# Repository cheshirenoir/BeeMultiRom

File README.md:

# BeeMultiRom
27c128 to 27c2001 adapter with selector for choosing between 16 different ROM images.
CC BY SA created in KiCAD
TESTED OK! If you use it in the IC22 socket of a PC85b, you can use double sized ROMs. If you use single sized ROMs, you can then access the lower ROM with PAK4 and the upper ROM with PAK12
This new version uses turned pins (from turned pin sockets. Just cut them mout with side cutters) and will just fit inside the case of a Microbee. 

Assembly instructions here: https://ilike8bits.com/assembling-the-microbee-multirom/

CC BY SA

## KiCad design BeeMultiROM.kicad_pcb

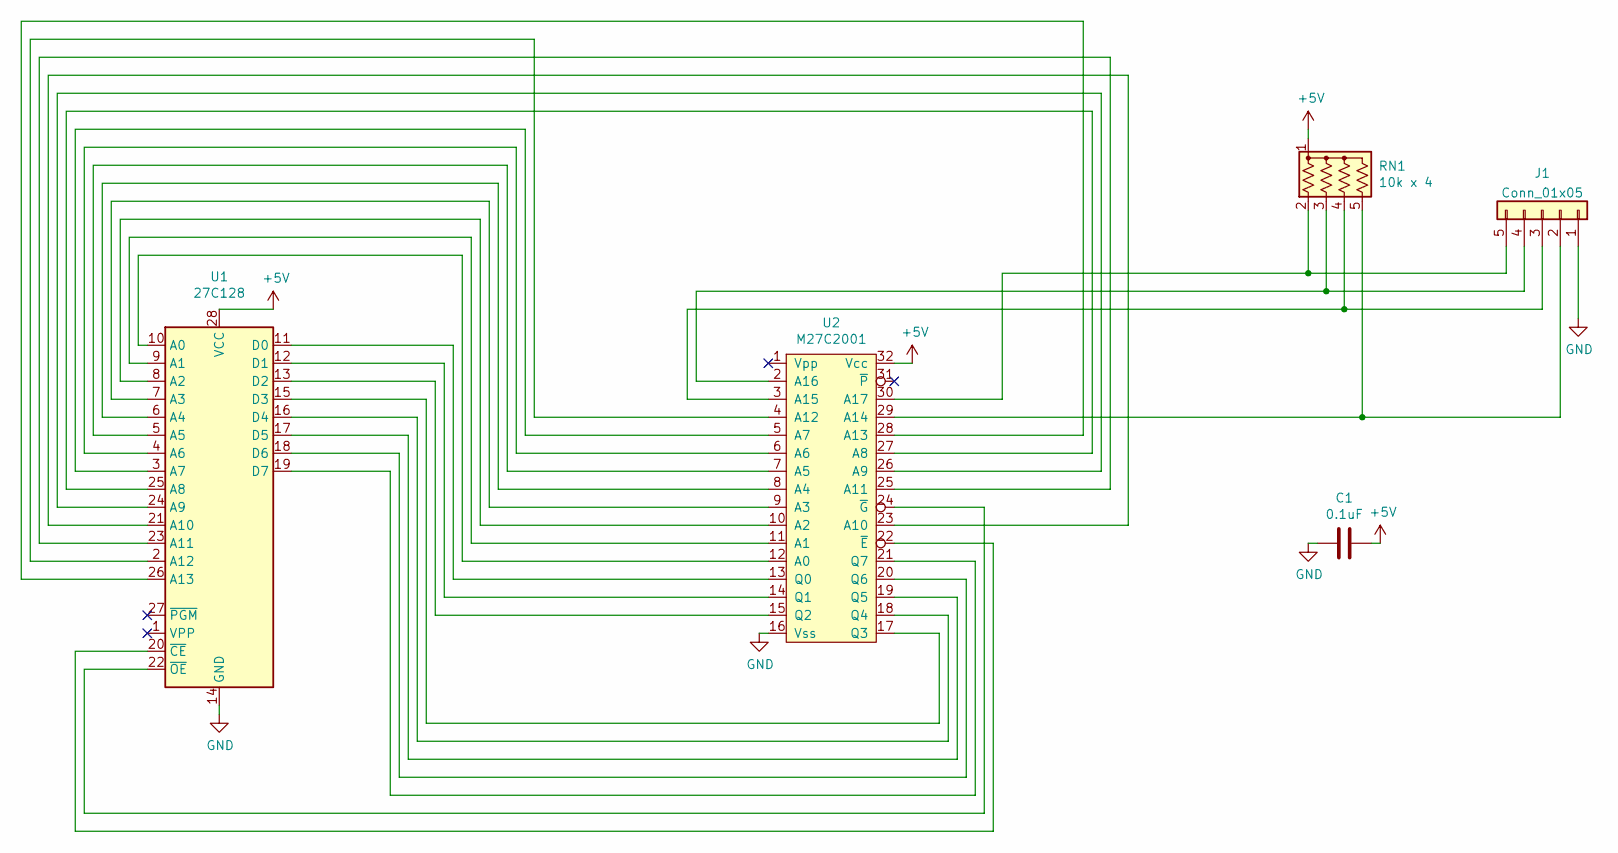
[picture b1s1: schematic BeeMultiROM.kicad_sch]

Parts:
C1: 0.1uF; C_Disc_D8.0mm_W2.5mm_P5.00mm
J1: Conn_01x05; PinHeader_1x05_P2.54mm_Vertical
RN1: 10k x 4; R_Array_SIP5
U1: 27C128; DIP-28_W15.24mm
U2: M27C2001; DIP-32_LP_FATBOY

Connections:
+5V: C1.1, RN1.1 (common), U1.28 (VCC), U2.32 (Vcc)
GND: C1.2, J1.1, U1.14 (GND), U2.16 (Vss)
unnamed: J1.2, RN1.5 (R4), U2.29 (A14)
unnamed: J1.3, RN1.4 (R3), U2.3 (A15)
unnamed: J1.4, RN1.3 (R2), U2.2 (A16)
unnamed: J1.5, RN1.2 (R1), U2.30 (A17)
unnamed: U1.2 (A12), U2.4 (A12)
unnamed: U1.3 (A7), U2.5 (A7)
unnamed: U1.4 (A6), U2.6 (A6)
unnamed: U1.5 (A5), U2.7 (A5)
unnamed: U1.6 (A4), U2.8 (A4)
unnamed: U1.7 (A3), U2.9 (A3)
unnamed: U1.8 (A2), U2.10 (A2)
unnamed: U1.9 (A1), U2.11 (A1)
unnamed: U1.10 (A0), U2.12 (A0)
unnamed: U1.11 (D0), U2.13 (Q0)
unnamed: U1.12 (D1), U2.14 (Q1)
unnamed: U1.13 (D2), U2.15 (Q2)
unnamed: U1.15 (D3), U2.17 (Q3)
unnamed: U1.16 (D4), U2.18 (Q4)
unnamed: U1.17 (D5), U2.19 (Q5)
unnamed: U1.18 (D6), U2.20 (Q6)
unnamed: U1.19 (D7), U2.21 (Q7)
unnamed: U1.20 (~CE), U2.22 (~E)
unnamed: U1.21 (A10), U2.23 (A10)
unnamed: U1.22 (~OE), U2.24 (~G)
unnamed: U1.23 (A11), U2.25 (A11)
unnamed: U1.24 (A9), U2.26 (A9)
unnamed: U1.25 (A8), U2.27 (A8)
unnamed: U1.26 (A13), U2.28 (A13)

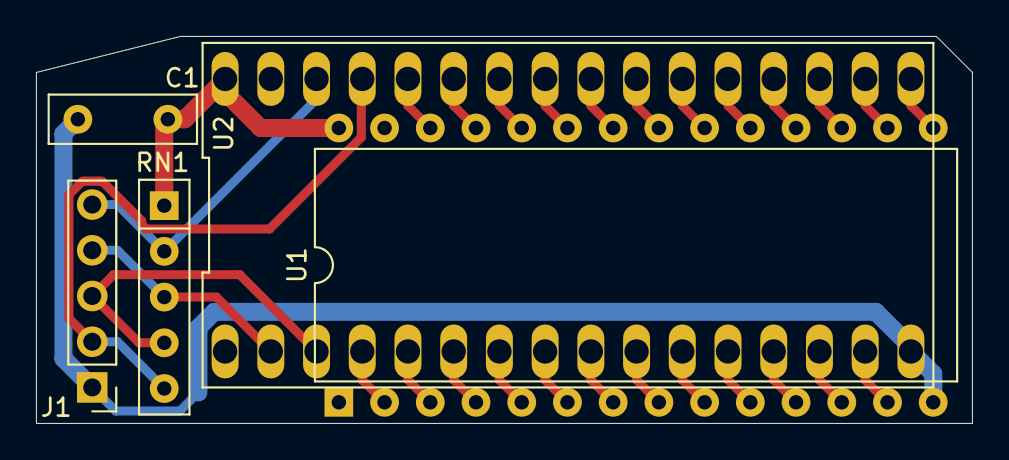
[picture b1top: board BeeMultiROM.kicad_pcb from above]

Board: 2 copper layers, 52.0 x 21.5 mm, 5 parts (0 on the bottom side), 30 nets.

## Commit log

2021-12-12 Add files via upload
    Initial version. CC BY SA
2022-03-18 Add files via upload
    Gerbers of the BeeMultiRom, successfully tested
2022-08-06 Add files via upload
    Super low profile version
2023-06-11 Update README.md
    Correcting outdated URL

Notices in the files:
BeeMultiROM.kicad_pcb:
by CheshireNoir CC BY SA
